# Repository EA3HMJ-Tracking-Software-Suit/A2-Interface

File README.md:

# USdigital A2 encoder interface to Modbus-RTU RS-485 interface

Interface based on the ESP32 S2 Mini microcontroller and the ESP32 S2 Mini library [eModbus](https://github.com/eModbus/eModbus).

It behaves as a modbus-RTU client with addresses 1 for azimuth and 2 for elevation at 115200 bauds and responding to function 3 and 6.

Register 0 returns a 32-bit number (two registers) which is the encoder position.

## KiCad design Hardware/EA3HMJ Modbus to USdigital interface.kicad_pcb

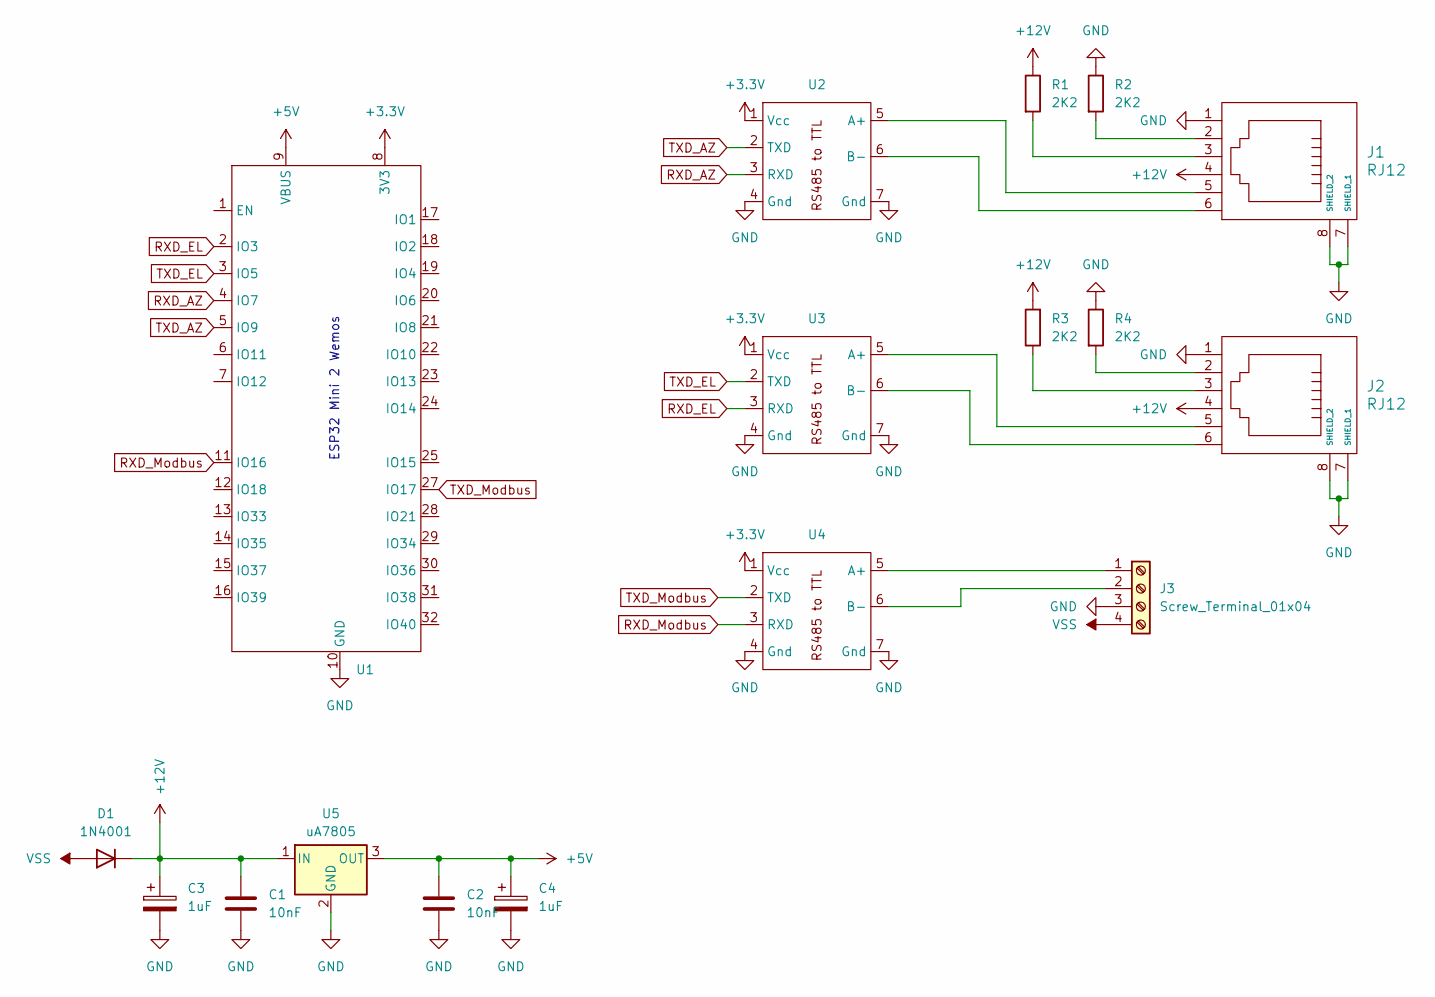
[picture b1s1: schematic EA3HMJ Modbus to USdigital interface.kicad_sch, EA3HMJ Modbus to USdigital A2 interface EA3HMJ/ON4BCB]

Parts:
C1, C2: 10nF; C_Disc_D3.0mm_W2.0mm_P2.50mm
C3, C4: 1uF; CP_Radial_D5.0mm_P2.50mm
D1: 1N4001; D_DO-41_SOD81_P10.16mm_Horizontal
J1, J2: RJ12; RJ12_Amphenol_54601
J3: Screw_Terminal_01x04; TerminalBlock_bornier-4_P5.08mm
R1, R2, R3, R4: 2K2; R_Axial_DIN0204_L3.6mm_D1.6mm_P7.62mm_Horizontal
U1: WEMOS_S2_mini
U2, U3, U4: RS485 to TTL
U5: uA7805; TO-220-3_Horizontal_TabDown

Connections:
+3.3V: U1.8 (3V3), U2.1 (Vcc), U3.1 (Vcc), U4.1 (Vcc)
+5V: C2.1, C4.1, U1.9 (VBUS), U5.3 (OUT)
+12V: C1.1, C3.1, D1.1 (K), J1.4, J2.4, R1.1, R3.2, U5.1 (IN)
GND: C1.2, C2.2, C3.2, C4.2, J1.1, J1.7 (SHIELD_1), J1.8 (SHIELD_2), J2.1, J2.7 (SHIELD_1), J2.8 (SHIELD_2), J3.3, R2.1, R4.1, U1.10 (GND), U2.4 (Gnd), U2.7 (Gnd), U3.4 (Gnd), U3.7 (Gnd), U4.4 (Gnd), U4.7 (Gnd), U5.2 (GND)
unnamed: J1.2, R2.2
unnamed: J1.3, R1.2
unnamed: J2.2, R4.2
unnamed: J2.3, R3.1
unnamed: J3.1, U4.5 (A+)
unnamed: J3.2, U4.6 (B-)
unnamed: J1.5, U2.5 (A+)
unnamed: J1.6, U2.6 (B-)
unnamed: J2.5, U3.5 (A+)
unnamed: J2.6, U3.6 (B-)
RXD_AZ: U1.4 (IO7), U2.3 (RXD)
RXD_EL: U1.2 (IO3), U3.3 (RXD)
RXD_Modbus: U1.11 (IO16), U4.3 (RXD)
TXD_AZ: U1.5 (IO9), U2.2 (TXD)
TXD_EL: U1.3 (IO5), U3.2 (TXD)
TXD_Modbus: U1.27 (IO17), U4.2 (TXD)
VSS: D1.2 (A), J3.4

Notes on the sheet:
ESP32 Mini 2 Wemos

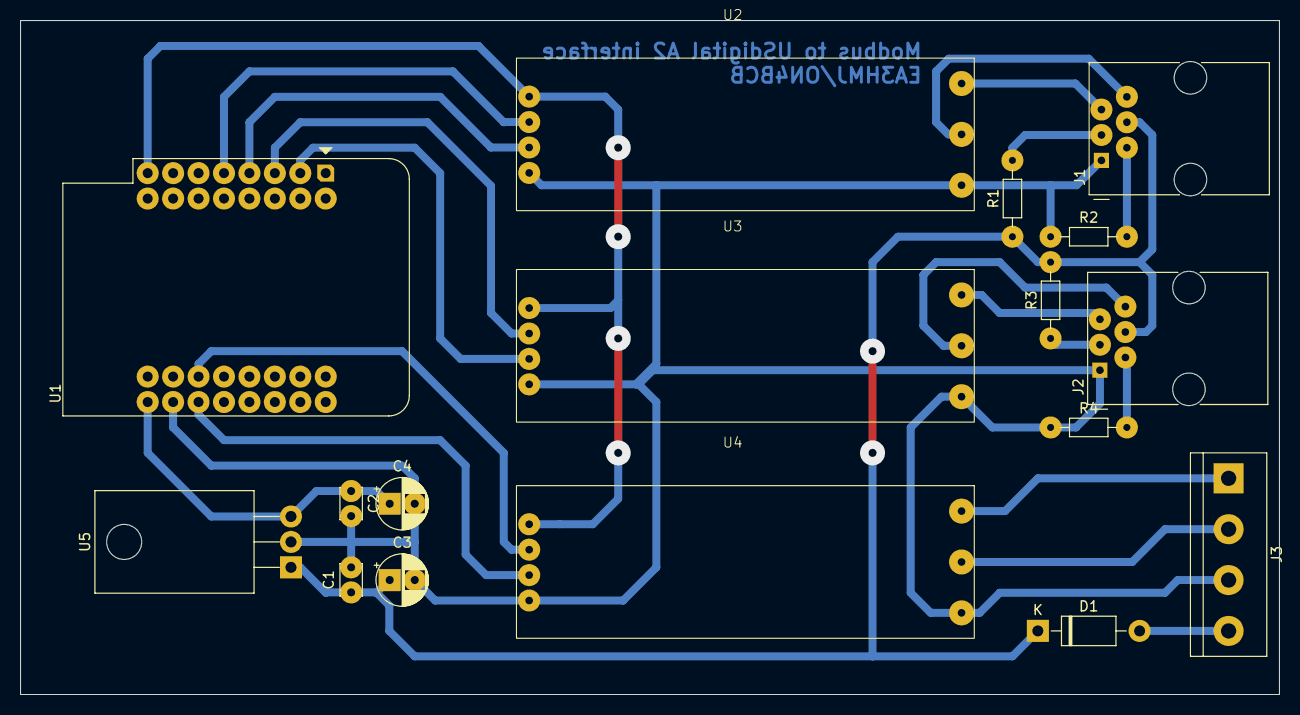
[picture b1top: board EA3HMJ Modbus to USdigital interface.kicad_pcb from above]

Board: 2 copper layers, 125.7 x 67.3 mm, 17 parts (0 on the bottom side), 21 nets.

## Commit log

2023-11-17 Add files via upload
    Walter ON4BCB deesigned
